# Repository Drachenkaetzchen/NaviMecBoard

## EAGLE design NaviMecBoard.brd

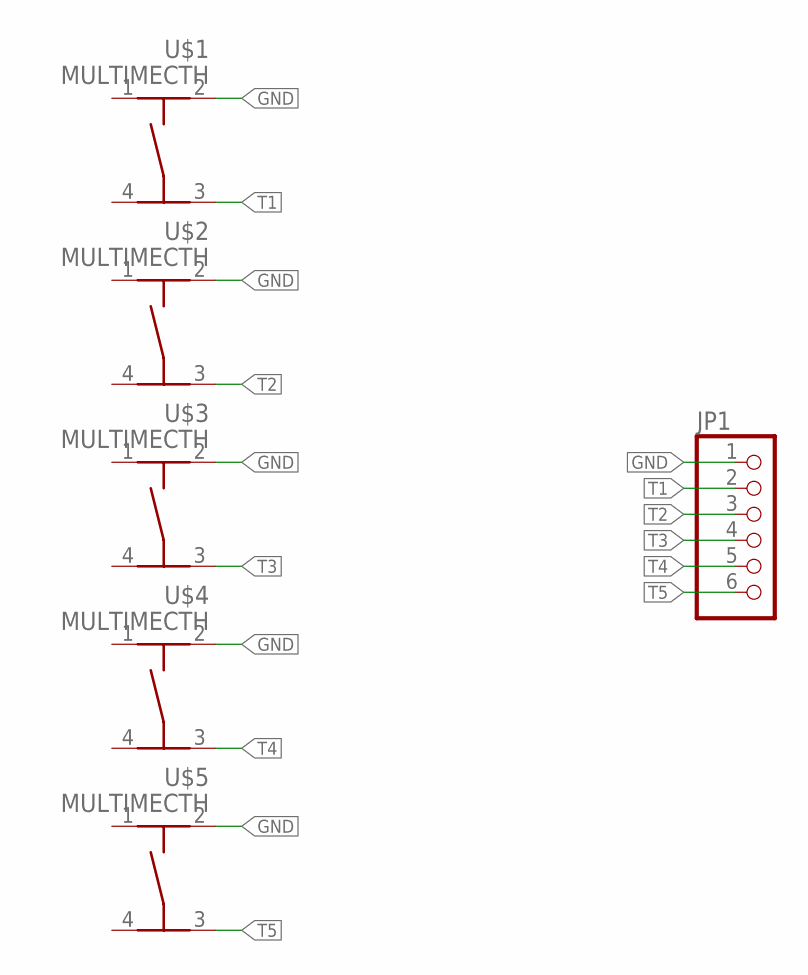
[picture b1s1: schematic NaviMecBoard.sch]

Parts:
JP1: PINHD-1X6; 1X06
U$1, U$2, U$3, U$4, U$5: MULTIMECTH; MULTIMEC_TH

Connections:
GND: JP1.1, U$1.2, U$2.2, U$3.2, U$4.2, U$5.2
T1: JP1.2, U$1.3 (4)
T2: JP1.3, U$2.3 (4)
T3: JP1.4, U$3.3 (4)
T4: JP1.5, U$4.3 (4)
T5: JP1.6, U$5.3 (4)

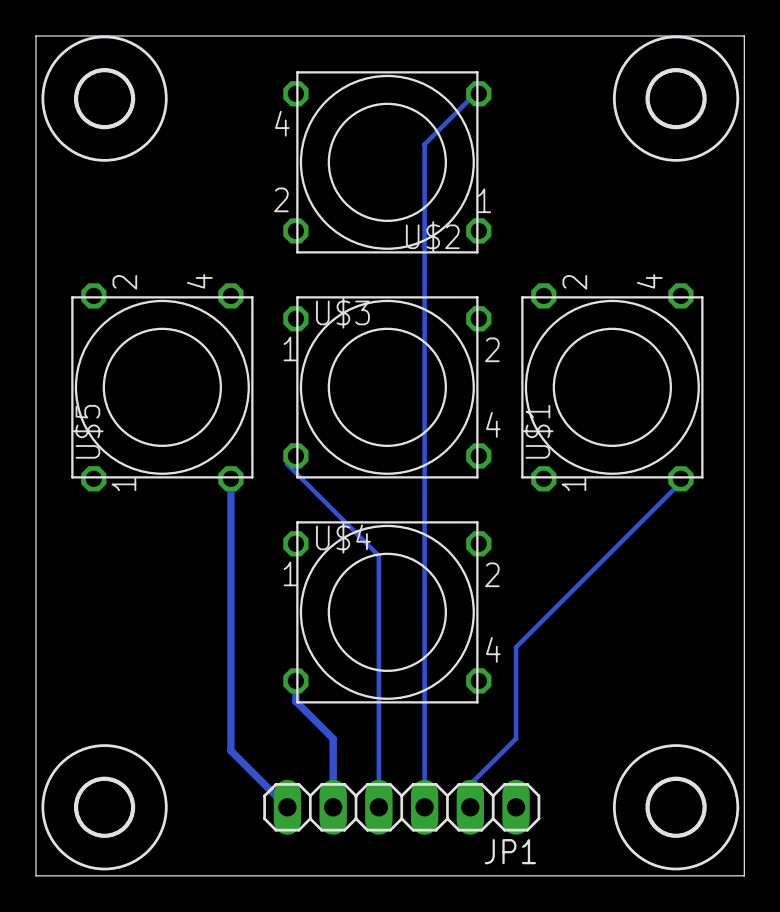
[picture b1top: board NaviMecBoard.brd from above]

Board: 2 copper layers, 39.3 x 46.7 mm, 10 parts (0 on the bottom side), 6 nets.

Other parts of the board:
U$6, U$7, U$8, U$9: 3,0
